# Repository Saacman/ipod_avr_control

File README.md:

# ipod_avr_control
The initial plan was to use `UART` to control the `KCX BT module`. But this has some downsides:
- Pin usage: It needs 2 pins for `RX/TX`, and an additional pin to wake up the BT module.
- Power Usage: Clock frequency needs to be at least `5MHz` to use achieve 9600 baud.
- Reliability: The serial interface of the BT Module is very unreliable.
- Complexity: It would be needed to track the states of the BT module with internal variables. A mismatch would be hard to debug in a permanent solution.
- Memory Usage: using the serial methods increases the memory usage by a lot. A lighter implementation would be needed, possibly introducing more possible errors/

I could revisit this option later.

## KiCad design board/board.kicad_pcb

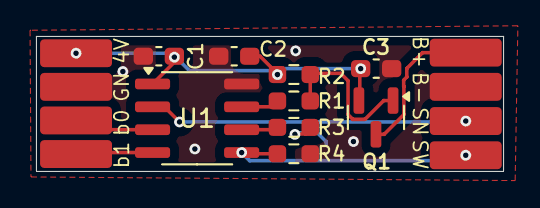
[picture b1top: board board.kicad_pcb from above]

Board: 2 copper layers, 26.0 x 7.5 mm, 12 parts (1 on the bottom side), 11 nets.

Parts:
C1: 100N; C_0603_1608Metric_Pad1.08x0.95mm_HandSolder
C2, C3: 10u; C_0603_1608Metric_Pad1.08x0.95mm_HandSolder
Q1: AO3401A; SOT-23
R1: 330; R_0603_1608Metric_Pad0.98x0.95mm_HandSolder
R2: 10k; R_0603_1608Metric_Pad0.98x0.95mm_HandSolder
R3, R4: 4.7k; R_0603_1608Metric_Pad0.98x0.95mm_HandSolder
TP1: TestPoint; TestPoint_Pad_D1.0mm
U1: ATtiny402-SS; SOIC-8_3.9x4.9mm_P1.27mm
U2: iPod_Custom
U3: BT_SW_Custom

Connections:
+4V: C1.1, C2.1, C3.1, Q1.2 (S), R2.2, U1.1 (VCC), U2.1 (Vcc)
GND: C1.2, C2.2, C3.2, R4.1, U1.8 (GND), U2.2 (GND), U3.2 (GND)
INT_SW: R4.2, U1.5 (PA2), U3.4 (SW_HOLD)
IO_BT: R1.2, U1.7 (PA3)
IO_BTTN0: U1.3 (PA7), U2.3 (Button0)
IO_BTTN1: U1.4 (PA1), U2.4 (Button1)
IO_SCAN: U1.2 (PA6), U3.3 (SCAN)
unnamed: Q1.1 (G), R1.1, R2.1
unnamed: R3.2, U1.6 (~RESET/PA0)
UPDI: R3.1, TP1.1
Vcc_BT: Q1.3 (D), U3.1 (VCC_BT)

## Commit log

2025-06-02 attempt to refactor
2025-06-02 finished fsm
2025-06-02 removed unused file
2025-06-02 added blocking button and events functions
2025-06-02 fixed integer type bug on dbl click
2025-06-12 uart demo
2025-06-12 added notes to readme
2025-06-17 added event queue, getter and reset method
2025-06-17 Added mosfet control and fixed glitches of enable button
2025-06-17 Extrbullet point
2025-06-19 implemented sleep and interrupt
2025-06-25 Created schematic and pcb design
2025-07-01 Added scan button handle
2025-07-01 Changed button inpout to use internal pull-ups
2025-07-01 fixed schematic and pcb
2025-07-01 pcb tweaks and gitignore
2025-07-01 added 4v via
2025-07-02 added methods to enable/disable pullups
2025-07-02 tried to implement different sleeping modes
2025-07-02 not working
2025-07-02 some cleaning
2025-07-02 cleaning
2025-07-03 changed gate logic to control p-mosfet
